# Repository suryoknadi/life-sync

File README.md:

# Apa itu Life Sync
<p align="center" style="font-size:38px"><strong>Sistem Monitoring Kesehatan Tubuh Berdasarkan Detak Jantung dan Suhu Tubuh berbasis Internet Of Things</strong></p>

Life Sync adalah  sebuah jaket pintar yang menggunakan teknologi Internet of Things (IoT) untuk memantau kondisi kesehatan pengguna secara real-time, terutama detak jantung dan suhu tubuh. Jaket ini dilengkapi dengan sensor yang tertanam di bagian dalam kain, yang secara otomatis mengukur parameter vital seperti detak jantung dan suhu tubuh.

# Features
- **Sensor Biometrik** : Jaket ini memiliki sensor yang terintegrasi untuk memantau detak jantung dan suhu tubuh secara akurat dan terus menerus.
- **Konektivitas IoT** : Data yang diperoleh dari sensor akan dikirim secara nirkabel ke smartphone atau perangkat lain yang terhubung melalui jaringan IoT, memungkinkan pemantauan jarak jauh oleh pengguna.
- **Aplikasi Pendukung** : Terdapat aplikasi mobile yang terhubung ke jaket ini untuk menampilkan data kesehatan secara real-time, dengan fitur notifikasi jika ada anomali seperti peningkatan suhu tubuh yang signifikan atau detak jantung yang tidak normal.

# The Stakeholders :
| **No**       | **Name**  | **Role**      |
|------------|------|-----------------|
| 1      | Arfin Nurur Robbi   | Hardware Developer       |
| 2        | M Suryo Nadi Pratama   | Back End Software Developer        |
| 3    | Dwiky Bagus Setyawan   | Front End Software Developer       |
| 4 | M Fani Tafazzul Hilmi | Product Design |
|5 | Ira Adi Nata | Firmware Development |

# Hardware

# Software

# Product Prototype
Berikut adalah ilustrasi tampilan dari produk kami :

# Rincian Biaya
|**Item**|**Jumlah**|**Harga Satuan (Rp)**|**Total (Rp)**|
|:--:|:--:|:--:|:--:|
|ESP32|1|150.000|150.000|
|LM35|2|30.000|60.000|
|Pulse Sensor|1|60.000|60.000|
|OLED|1|50.000|50.000|
|Cloud Firebase|-|0|0|
|Baterai 18650 + Modul Charger|1|100.000|100.000|
|Total Biaya|---|---|**420.000**|

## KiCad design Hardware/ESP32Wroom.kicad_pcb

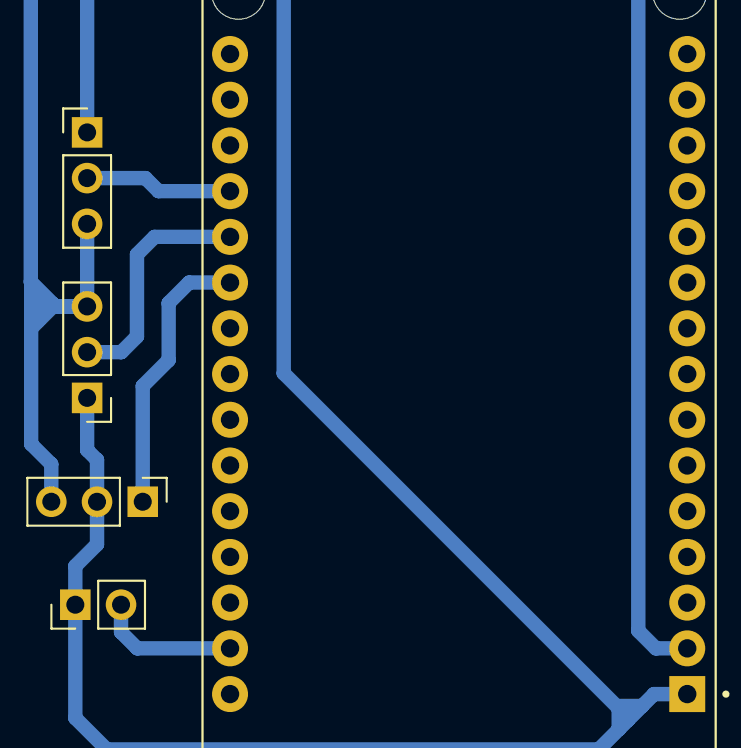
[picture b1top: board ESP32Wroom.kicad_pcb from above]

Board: 2 copper layers, 5 parts (0 on the bottom side), 5 nets.

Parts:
J1: Pin Baterai; PinHeader_1x02_P2.54mm_Vertical
PulseSensor: SEN-11574; PinHeader_1x03_P2.54mm_Vertical
U1: ESP32-DEVKIT-V1; MODULE_ESP32_DEVKIT_V1
U2, U3: LM35-LP; PinHeader_1x03_P2.54mm_Vertical

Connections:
GND: J1.2, PulseSensor.3 (GND), U1.2 (GND), U1.29 (GND), U2.3 (GND), U3.3 (GND)
LM1: U1.19 (D34), U2.2 (V_{OUT})
LM2: U1.20 (D35), U3.2 (V_{OUT})
PS: PulseSensor.1 (SIGNAL), U1.21 (D32)
Vs: J1.1, PulseSensor.2 (V+), U1.1 (3V3), U2.1 (+V_{S}), U3.1 (+V_{S})

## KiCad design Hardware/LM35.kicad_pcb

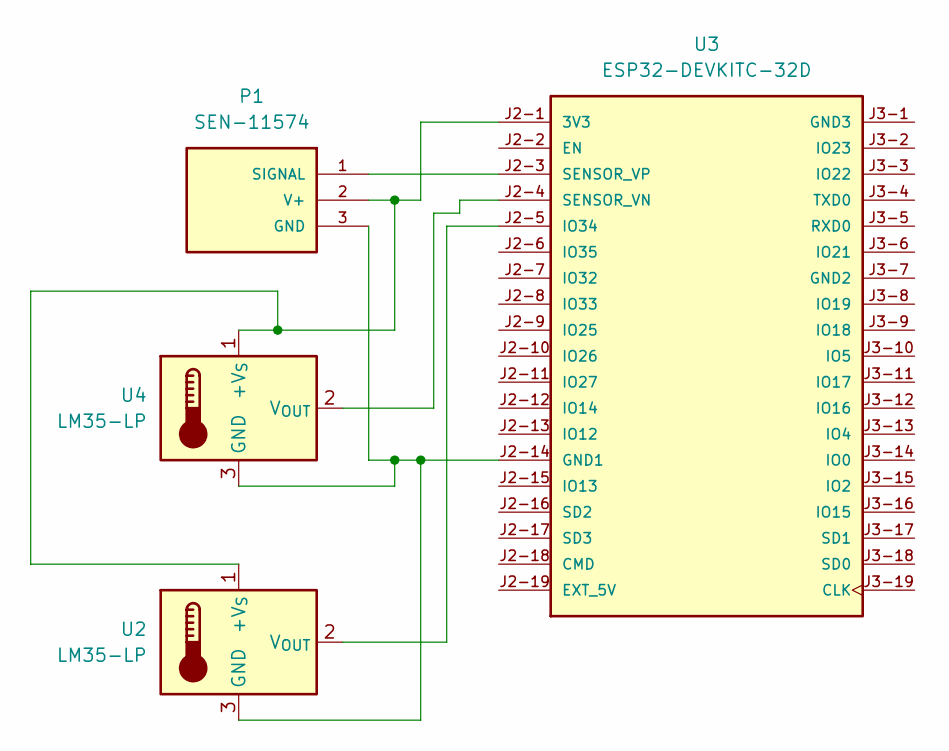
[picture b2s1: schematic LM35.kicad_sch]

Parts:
P1: SEN-11574; XDCR_SEN-11574
U2, U4: LM35-LP; TO-92_Inline
U3: ESP32-DEVKITC-32D; MODULE_ESP32-DEVKITC-32D; PARTREV V4

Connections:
unnamed: P1.3 (GND), U2.3 (GND), U3.J2-14 (GND1), U4.3 (GND)
unnamed: P1.1 (SIGNAL), U3.J2-3 (SENSOR_VP)
unnamed: P1.2 (V+), U2.1 (+V_{S}), U3.J2-1 (3V3), U4.1 (+V_{S})
unnamed: U2.2 (V_{OUT}), U3.J2-5 (IO34)
unnamed: U3.J2-4 (SENSOR_VN), U4.2 (V_{OUT})

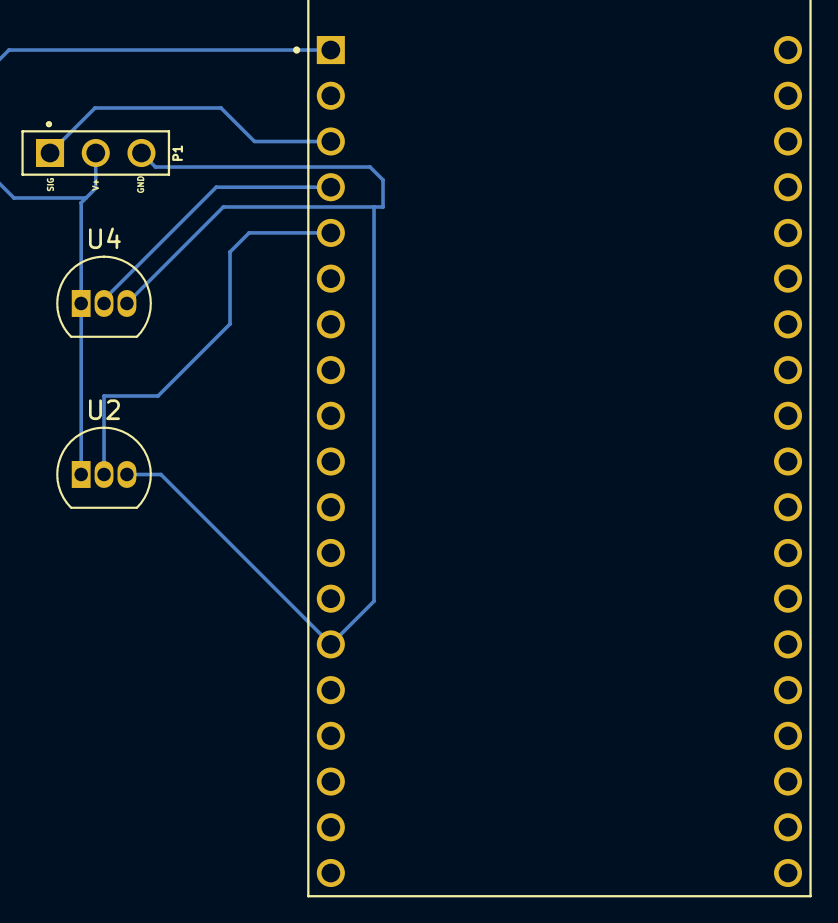
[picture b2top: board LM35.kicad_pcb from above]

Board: 2 copper layers, 4 parts (0 on the bottom side), 5 nets.

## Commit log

2024-10-07 Life Sync Logo
2024-10-07 Create Assets
2024-10-07 Create Assets-null
2024-10-07 Rename README.md to Description.md
2024-10-07 Rename Description.md to Readme.md
2024-10-12 Menambahkan folder Assets dengan gambar
2024-10-12 Menambahkan beberapa gambar pada assets
2024-10-12 Melakukan perubahan file Readme.md
2024-10-12 Menambahkan gambar diagram alir
2024-10-12 Menambahkan beberapa perubahan dan penyesuaian
2024-10-14 Add files via upload
    Add new program firmware
2024-10-14 Add files via upload
    Add Proposal and PPT
2024-10-14 mistake
2024-10-14 Delete Documents/life-sync directory
    mistake
2024-10-14 Add New Program Firmware, Proposal, PPT
    Add New Program Firmware, Proposal, PPT
2024-10-14 Menambahkan file hardware
2024-10-14 Menghapus Hardware
2024-10-14 Menambahkan folder Hardware
2024-10-14 Menambahkan PCB dan Schematic, Memodifikasi bagian Hardware pada Readme
2024-10-14 Melakukan modifikasi pada readme dan Menambahkan gambar PCB dan Schematic
2024-10-14 Melakukan modifikasi format gambar
2024-10-14 Modifikasi file readme.md
2024-10-21 Add files via upload
    menambahkan design sementara jaket 2D
2024-10-21 Delete life-sync-fani directory
    salah
2024-11-02 edit program contains connect wifi, connect MQTT
2024-11-02 Foto Simulasi
2024-11-07 add management wifi
2024-11-07 Add Webhook to send data to Firebase
2024-11-07 add pic MQTT Shiftr.io
2024-11-09 Penambahan desain PCB
2024-11-10 add foto team
2024-11-10 change program to implement using sensor
2024-11-10 menambahkan foto product
2024-11-10 menambahkan video project
2024-11-10 menambahkan video product
2024-11-10 PPT Monev Sementara
2024-11-10 before implement on jacet
2024-11-10 foto anggota
2024-11-10 menambahkan foto pengujian sensor
2024-11-10 Menambahkan Logo Life-Sync
2024-11-10 Menambahkan Screenshot Halaman Web
2024-11-11 Menambahkan Foto Dosen
2024-11-11 Melakukan Update Readme
2024-11-11 Melakukan Update Readme.md
2024-11-15 change code
2024-11-15 a just upload, because crash
2024-11-15 PPT Monev Compress Zip
2024-11-15 Last program wrong, so right now is true
2024-11-15 PPT Monev on 18 November 2024
